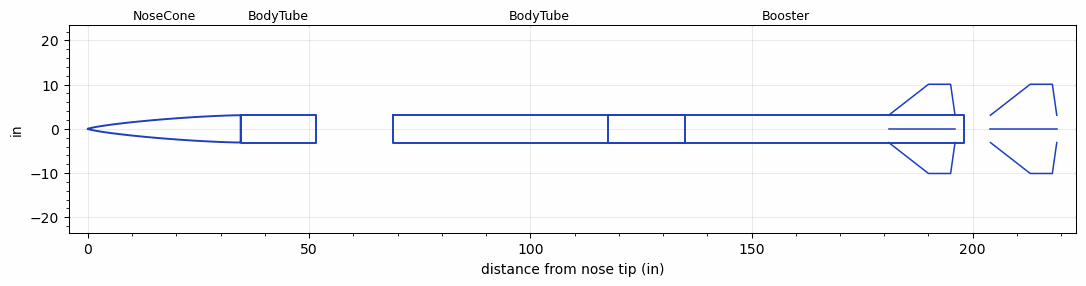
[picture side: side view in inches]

<RASAeroDocument>
 <FileVersion>2</FileVersion>
 <RocketDesign>
  <NoseCone>
   <Length>34.5</Length>
   <Diameter>6.17</Diameter>
   <Shape>Von Karman Ogive</Shape>
   <Location>0</Location>
  </NoseCone>
  <BodyTube>
   <Length>17</Length>
   <Diameter>6.17</Diameter>
   <Location>34.5</Location>
  </BodyTube>
  <BodyTube>
   <Length>66</Length>
   <Diameter>6.17</Diameter>
   <Location>69</Location>
   <Fin>
    <Count>4</Count>
    <Chord>15</Chord>
    <Span>7</Span>
    <SweepDistance>9</SweepDistance>
    <TipChord>5</TipChord>
    <Thickness>0.5</Thickness>
    <LERadius>0.5</LERadius>
    <Location>-69</Location>
    <AirfoilSection>Double Wedge</AirfoilSection>
    <FX1>1</FX1>
    <FX3>1</FX3>
   </Fin>
  </BodyTube>
  <Booster>
   <Length>80.5</Length>
   <Diameter>6.17</Diameter>
   <InsideDiameter>6.17</InsideDiameter>
   <Location>117.5</Location>
   <ShoulderLength>0</ShoulderLength>
   <Fin>
    <Count>4</Count>
    <Chord>15</Chord>
    <Span>7</Span>
    <SweepDistance>9</SweepDistance>
    <TipChord>5</TipChord>
    <Thickness>0.5</Thickness>
    <LERadius>0.5</LERadius>
    <Location>17</Location>
    <AirfoilSection>Double Wedge</AirfoilSection>
    <FX1>1</FX1>
    <FX3>1</FX3>
   </Fin>
  </Booster>
  <Surface>Smooth (Zero Roughness)</Surface>
  <ModifiedBarrowman>False</ModifiedBarrowman>
  <Turbulence>False</Turbulence>
  <UseBooster1>False</UseBooster1>
  <UseBooster2>False</UseBooster2>
 </RocketDesign>
 <LaunchSite>
  <Altitude>2050</Altitude>
  <Pressure>0</Pressure>
  <RodAngle>0</RodAngle>
  <RodLength>24</RodLength>
  <Temperature>90</Temperature>
  <WindSpeed>0</WindSpeed>
 </LaunchSite>
 <Recovery>
  <Altitude1>1000</Altitude1>
  <Altitude2>1000</Altitude2>
  <DeviceType1>Parachute</DeviceType1>
  <DeviceType2>None</DeviceType2>
  <Event1>True</Event1>
  <Event2>False</Event2>
  <Size1>48</Size1>
  <Size2>1</Size2>
  <EventType1>Apogee</EventType1>
  <EventType2>None</EventType2>
  <CD1>0.97</CD1>
  <CD2>1.33</CD2>
 </Recovery>
 <SimulationList>
  <Simulation>
   <SustainerEngine>TBDPS-21  (GTXR)</SustainerEngine>
   <SustainerLaunchWt>117.9</SustainerLaunchWt>
   <SustainerNozzleDiameter>4.18</SustainerNozzleDiameter>
   <SustainerCG>80.19</SustainerCG>
   <SustainerIgnitionDelay>20</SustainerIgnitionDelay>
   <Booster1Engine>TBDPS-21  (GTXR)</Booster1Engine>
   <Booster1LaunchWt>224.93</Booster1LaunchWt>
   <Booster1SeparationDelay>2</Booster1SeparationDelay>
   <Booster1IgnitionDelay>0</Booster1IgnitionDelay>
   <Booster1CG>120.83</Booster1CG>
   <Booster1NozzleDiameter>4.18</Booster1NozzleDiameter>
   <IncludeBooster1>True</IncludeBooster1>
   <Booster2Delay>0</Booster2Delay>
   <IncludeBooster2>False</IncludeBooster2>
   <TimetoApogee>107.1723</TimetoApogee>
   <MaxAltitude>117556.6</MaxAltitude>
   <MaxVelocity>3034.942</MaxVelocity>
   <OptimumWt>81.71671</OptimumWt>
   <OptimumMaxAlt>81.71671</OptimumMaxAlt>
  </Simulation>
 </SimulationList>
</RASAeroDocument>
